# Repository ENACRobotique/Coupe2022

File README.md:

# Coupe2022
Ficihiers de KiCAD et autres pour la coupe de robotique 2022 (Age of Bots)

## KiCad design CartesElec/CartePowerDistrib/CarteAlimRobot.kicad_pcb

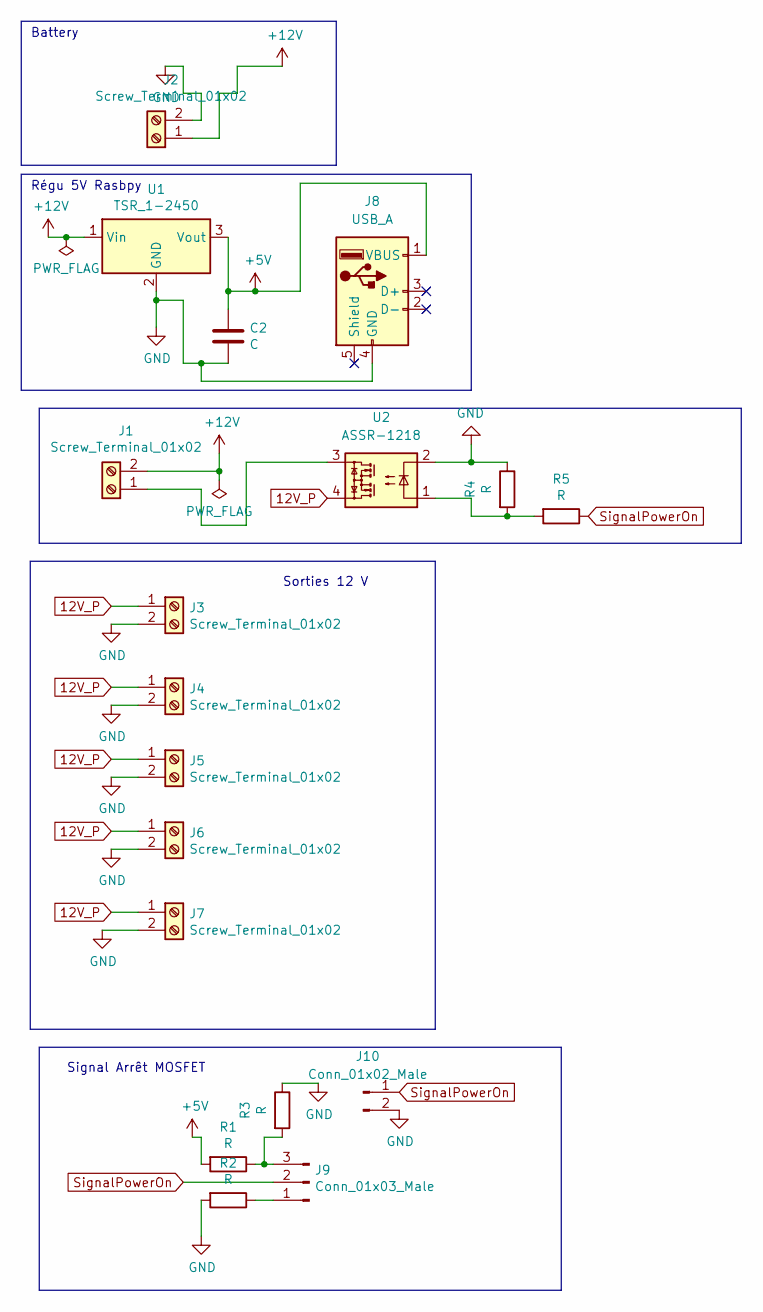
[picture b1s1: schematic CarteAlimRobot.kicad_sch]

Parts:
C2: C; C_0805_2012Metric
J1, J2, J3, J4, J5, J6, J7: Screw_Terminal_01x02; TerminalBlock_bornier-2_P5.08mm
J8: USB_A; USB_A_Molex_67643_Horizontal
J9: Conn_01x03_Male; JST_XH_B3B-XH-AM_1x03_P2.50mm_Vertical
J10: Conn_01x02_Male; JST_EH_B2B-EH-A_1x02_P2.50mm_Vertical
R1, R2, R3, R4, R5: R; R_0805_2012Metric
U1: TSR_1-2450; Converter_DCDC_TRACO_TSR-1_THT
U2: ASSR-1218; SO-4_4.4x3.6mm_P2.54mm

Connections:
12V_P: J3.1, J4.1, J5.1, J6.1, J7.1, U2.4
+5V: C2.1, J8.1 (VBUS), R1.2, U1.3 (Vout)
+12V: J1.2, J2.1, U1.1 (Vin)
GND: C2.2, J2.2, J3.2, J4.2, J5.2, J6.2, J7.2, J8.4 (GND), J10.2, R2.2, R3.1, R4.1, U1.2 (GND), U2.2
unnamed: J1.1, U2.3
unnamed: J9.1, R2.1
unnamed: J9.3, R1.1, R3.2
unnamed: R4.2, R5.2, U2.1
SignalPowerOn: J9.2, J10.1, R5.1

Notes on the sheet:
Sorties 12 V
Battery
Régu 5V Rasbpy
Signal Arrêt MOSFET

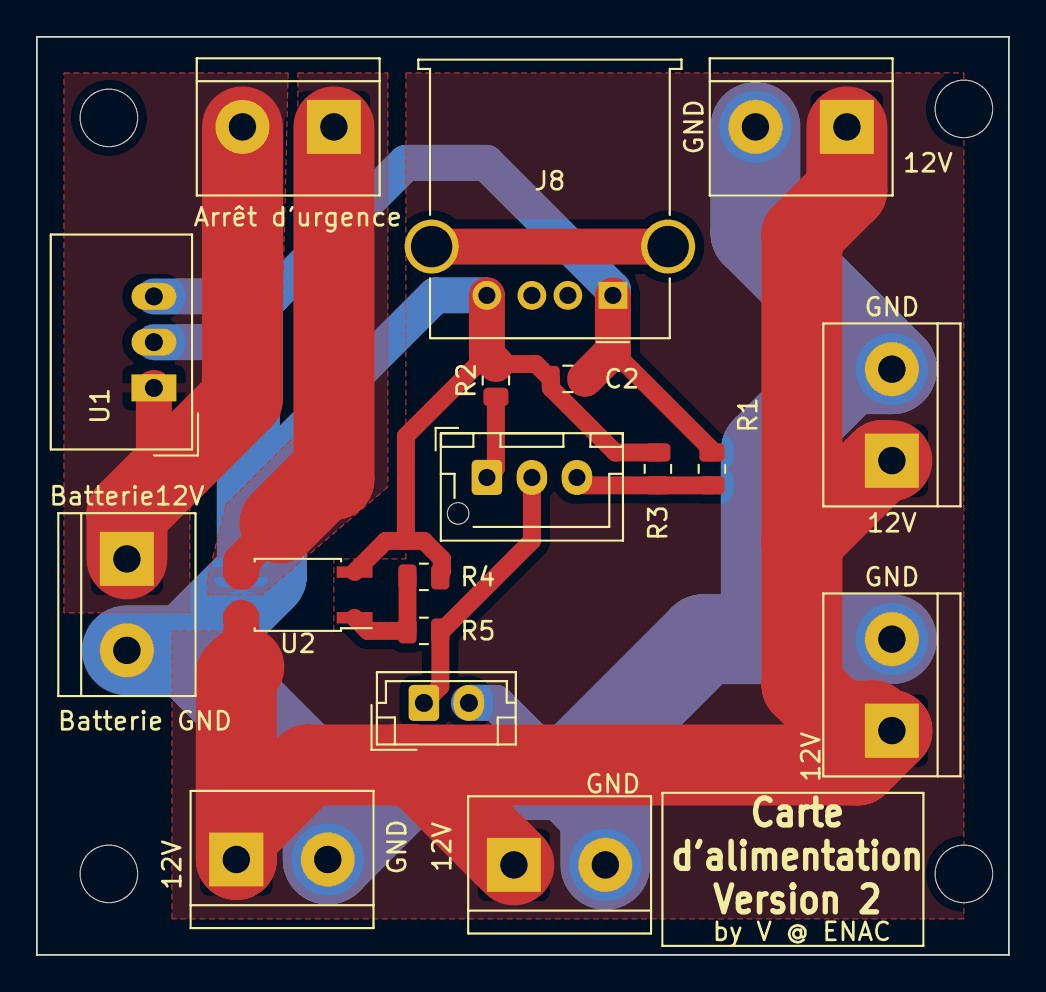
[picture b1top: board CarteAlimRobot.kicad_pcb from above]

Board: 2 copper layers, 54.0 x 51.0 mm, 18 parts (0 on the bottom side), 9 nets.

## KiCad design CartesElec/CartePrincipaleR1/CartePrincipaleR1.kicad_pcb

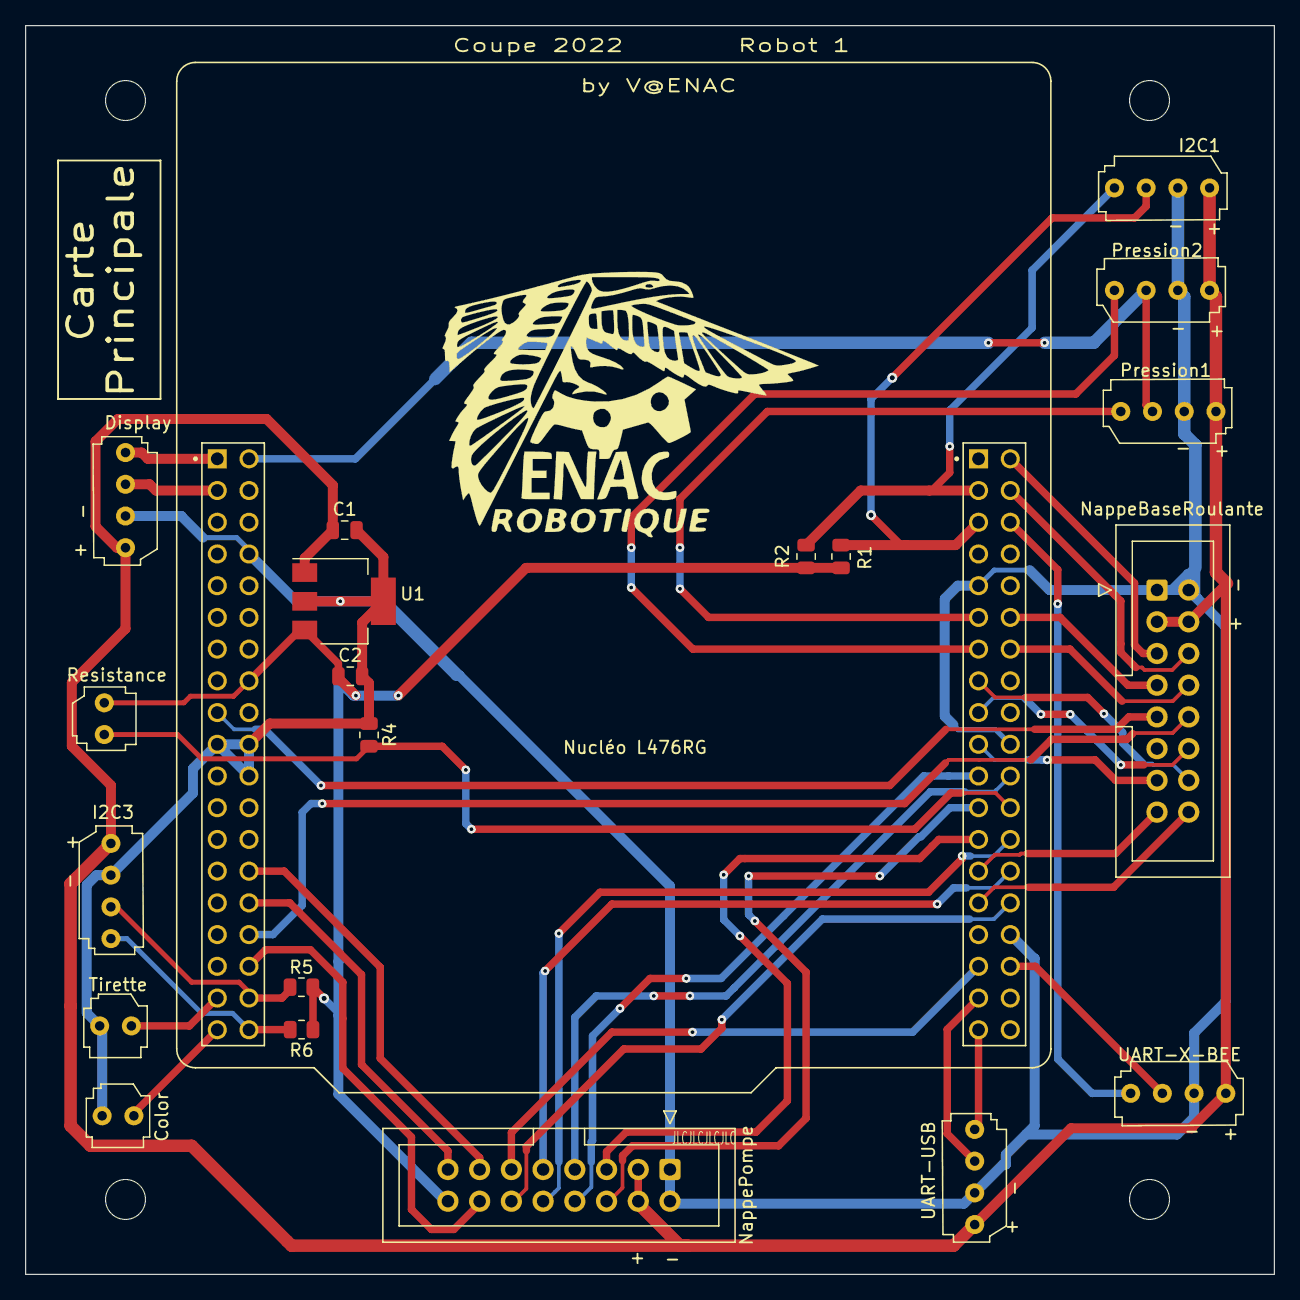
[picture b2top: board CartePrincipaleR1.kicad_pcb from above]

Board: 2 copper layers, 100.0 x 100.0 mm, 21 parts (0 on the bottom side), 41 nets.

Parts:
C1: 100n; C_0805_2012Metric
C2: 10u; C_0805_2012Metric
Color: Conn_01x02_Male; HE14_EMBASE_1x02
Display: Conn_01x04_Male; HE14_EMBASE_1x04
I2C1, I2C3: I2C; HE14_EMBASE_1x04
NappeBaseRoulante: Conn_02x08_Top_Bottom; IDC-Header_2x08_P2.54mm_Vertical
NappePompe: Conn_02x08_Top_Bottom; IDC-Header_2x08_P2.54mm_Vertical
Nucléo L476RG: NUCLEO64-F411RE; ST_NUCLEO-F401RE
Pression1, Pression2: Conn_01x04_Male; HE14_EMBASE_1x04
R1, R2, R5, R6: 2.2k; R_0805_2012Metric
R4: 1k; R_0805_2012Metric
Resistance: Conn_01x02_Male; HE14_EMBASE_1x02
Tirette: Conn_01x02_Male; HE14_EMBASE_1x02
U1: LT1129-3.3_SOT223; SOT-223-3_TabPin2
UART-USB: UART; HE14_EMBASE_1x04
UART-X-BEE: UART; HE14_EMBASE_1x04

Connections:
+3V3: C2.1, NappePompe.16, Nucléo L476RG.16 (+3V3), R1.1, R2.1, R5.1, R6.1, Resistance.1, U1.3 (VO)
+5V: C1.1, Display.1, I2C1.1, I2C3.1, NappeBaseRoulante.3, NappeBaseRoulante.4, NappePompe.3, NappePompe.4, Pression1.4, Pression2.4, U1.1 (VI), UART-USB.1, UART-X-BEE.1
A_Resistance: Nucléo L476RG.62 (PB1), R4.2, Resistance.2
CLK_Display: Display.4, Nucléo L476RG.1 (PC10)
CLK_PRESS: Nucléo L476RG.2 (PC11), Pression1.2, Pression2.2
COL_GPIO: Color.1, Nucléo L476RG.37 (PC3)
CONTACTEUR1_GPIO: NappeBaseRoulante.9, Nucléo L476RG.17 (PA15)
CONTACTEUR2_GPIO: NappeBaseRoulante.10, Nucléo L476RG.32 (PA4)
DATA_PRESS_1: Nucléo L476RG.49 (PA5), Pression1.1
DATA_PRESS_2: Nucléo L476RG.51 (PA6), Pression2.1
DIO_Display: Display.3, Nucléo L476RG.3 (PC12)
DataAX12_TX: NappeBaseRoulante.12, Nucléo L476RG.55 (PB6)
EV1: NappePompe.12, Nucléo L476RG.68 (PB13)
EV2: NappePompe.11, Nucléo L476RG.71 (PA10)
GND: C1.2, C2.2, Color.2, Display.2, I2C1.2, I2C3.2, NappeBaseRoulante.1, NappeBaseRoulante.2, NappePompe.1, NappePompe.2, Nucléo L476RG.8 (GND), Nucléo L476RG.19 (GND), Nucléo L476RG.20 (GND), Nucléo L476RG.22 (GND), Nucléo L476RG.47 (GND), Nucléo L476RG.58 (GND), Nucléo L476RG.70 (AGND), Pression1.3, Pression2.3, R4.1, Tirette.2, U1.2 (GND), UART-USB.2, UART-X-BEE.2
MC1A: NappeBaseRoulante.6, Nucléo L476RG.42 (PC6)
MC1B: NappeBaseRoulante.5, Nucléo L476RG.40 (PC8)
MC2A: NappeBaseRoulante.8, Nucléo L476RG.52 (PA11)
MC2B: NappeBaseRoulante.7, Nucléo L476RG.50 (PA12)
Mot1DIR: NappePompe.7, Nucléo L476RG.60 (PB2)
Mot1PWM: NappePompe.8, Nucléo L476RG.59 (PA9)
Mot2DIR: NappePompe.5, Nucléo L476RG.63 (PB10)
Mot2PWM: NappePompe.6, Nucléo L476RG.61 (PA8)
POMPE1: NappePompe.9, Nucléo L476RG.66 (PB14)
POMPE2: NappePompe.10, Nucléo L476RG.64 (PB15)
RC_1A: NappeBaseRoulante.16, Nucléo L476RG.67 (PB5)
RC_1B: NappeBaseRoulante.15, Nucléo L476RG.65 (PB4)
RC_2A: NappeBaseRoulante.14, Nucléo L476RG.53 (PA7)
RC_2B: NappeBaseRoulante.13, Nucléo L476RG.57 (PC7)
S1: NappePompe.13, Nucléo L476RG.28 (PA0)
S2: NappePompe.15, Nucléo L476RG.30 (PA1)
S3: NappePompe.14, Nucléo L476RG.34 (PB0)
SCL_I2C1: I2C1.4, Nucléo L476RG.41 (PB8), R2.2
SCL_I2C3: I2C3.4, Nucléo L476RG.38 (PC0), R6.2
SDA_I2C1: I2C1.3, Nucléo L476RG.43 (PB9), R1.2
SDA_I2C3: I2C3.3, Nucléo L476RG.36 (PC1), R5.2
TIR_GPIO: Nucléo L476RG.35 (PC2), Tirette.1
USART_RX: Nucléo L476RG.75 (STLINK_UART_RX/PA3), UART-USB.4
USART_TX: Nucléo L476RG.73 (STLINK_UART_TX/PA2), UART-USB.3
XBeeTx: Nucléo L476RG.72 (PC4), UART-X-BEE.3
XbeeRx: Nucléo L476RG.44 (PC5), UART-X-BEE.4

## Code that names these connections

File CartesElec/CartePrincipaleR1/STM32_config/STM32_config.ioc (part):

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Mcu.Name=STM32L476R(C-E-G)Tx
Mcu.Package=LQFP64
Mcu.UserName=STM32L476RGTx
PA0.Signal=S_TIM2_CH1
PA1.Signal=S_TIM2_CH2
PA13\ (JTMS-SWDIO).GPIOParameters=GPIO_Label
PA13\ (JTMS-SWDIO).GPIO_Label=TMS
PA13\ (JTMS-SWDIO).Mode=Serial_Wire
PA13\ (JTMS-SWDIO).Signal=SYS_JTMS-SWDIO
PA14\ (JTCK-SWCLK).GPIOParameters=GPIO_Label
PA14\ (JTCK-SWCLK).GPIO_Label=TCK
PA14\ (JTCK-SWCLK).Mode=Serial_Wire
PA14\ (JTCK-SWCLK).Signal=SYS_JTCK-SWCLK
PA2.GPIOParameters=GPIO_Speed,GPIO_PuPd,GPIO_Label,GPIO_Mode
PA2.GPIO_Label=USART_TX
PA2.GPIO_Mode=GPIO_MODE_AF_PP
PA2.GPIO_PuPd=GPIO_NOPULL
PA2.GPIO_Speed=GPIO_SPEED_FREQ_VERY_HIGH
PA2.Mode=Asynchronous
PA2.Signal=USART2_TX
PA3.GPIOParameters=GPIO_Speed,GPIO_PuPd,GPIO_Label,GPIO_Mode
PA3.GPIO_Label=USART_RX
PA3.GPIO_Mode=GPIO_MODE_AF_PP
PA3.GPIO_PuPd=GPIO_NOPULL
PA3.GPIO_Speed=GPIO_SPEED_FREQ_VERY_HIGH
PA3.Mode=Asynchronous
PA3.Signal=USART2_RX
PA5.GPIOParameters=GPIO_Speed,GPIO_PuPd,GPIO_Label,GPIO_ModeDefaultOutputPP
PA5.GPIO_Label=LD2 [green Led]
PA5.GPIO_ModeDefaultOutputPP=GPIO_MODE_OUTPUT_PP
PA5.GPIO_PuPd=GPIO_NOPULL
PA5.GPIO_Speed=GPIO_SPEED_FREQ_LOW
PA5.Signal=GPIO_Output
PA8.GPIOParameters=GPIO_Label
PA8.GPIO_Label=MOT2PWM
PA8.Signal=S_TIM1_CH1
PA9.GPIOParameters=GPIO_Label
PA9.GPIO_Label=MOT1PWM
PA9.Signal=S_TIM1_CH2
PB10.GPIOParameters=GPIO_Label
PB10.GPIO_Label=MOT2DIR
PB10.Signal=GPIO_Output
PB3\ (JTDO-TRACESWO).GPIOParameters=GPIO_Label
PB3\ (JTDO-TRACESWO).GPIO_Label=SWO
PB3\ (JTDO-TRACESWO).Signal=SYS_JTDO-SWO
PC0.Signal=I2C3_SCL
PC1.Signal=I2C3_SDA
PC13.GPIOParameters=GPIO_PuPd,GPIO_Label,GPIO_ModeDefaultEXTI
PC13.GPIO_Label=B1 [Blue PushButton]
PC13.GPIO_ModeDefaultEXTI=GPIO_MODE_IT_FALLING
PC13.GPIO_PuPd=GPIO_NOPULL
PC13.Signal=GPXTI13
PC14-OSC32_IN\ (PC14).Mode=LSE-External-Oscillator
PC14-OSC32_IN\ (PC14).Signal=RCC_OSC32_IN
PC15-OSC32_OUT\ (PC15).Mode=LSE-External-Oscillator
PC15-OSC32_OUT\ (PC15).Signal=RCC_OSC32_OUT
PC4.GPIOParameters=GPIO_Label
PC4.GPIO_Label=ADC_2
PC4.Signal=ADCx_IN13
PC5.GPIOParameters=GPIO_Label
PC5.GPIO_Label=ADC_1
PC5.Signal=ADCx_IN14
PC6.GPIOParameters=GPIO_Label
PC6.GPIO_Label=MOT1_ENC_A
PC6.Signal=GPIO_Input
PC7.GPIOParameters=GPIO_Label
PC7.GPIO_Label=MOT1DIR
PC7.Signal=GPIO_Output
PH0-OSC_IN\ (PH0).Signal=RCC_OSC_IN
PH1-OSC_OUT\ (PH1).Signal=RCC_OSC_OUT
RCC.HSE_VALUE=8000000
RCC.SYSCLKFreq_VALUE=80000000
RCC.SYSCLKSource=RCC_SYSCLKSOURCE_PLLCLK
board=NUCLEO-L476RG
boardIOC=true

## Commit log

2021-10-24 Début du Répo
2021-10-24 Mise à jour du PCB + début d'optimisation
2021-10-24 Optimisation d'espace sur la carte d'alim
2021-10-24 Save
2022-01-18 Ajout d'un nouveau projet
2022-01-18 fin de la carte d'alim
2022-01-18 Changement de description
2022-01-27 update maybe?
2022-01-29 update carte nucleo F411RE
2022-01-30 update hierarchical
2022-02-01 small updates
2022-02-02 [carte robot 1] finish schematic.
2022-02-02 Add HE14 footprints.
2022-02-03 Carte principale finie
2022-02-03 Ajout de textes au PCB
2022-02-03 carte secondair update
2022-02-03 secondaire update
2022-02-03 error fix
2022-02-03 footprint fixes
2022-02-03 gereber update
2022-02-04 Ajout de la date
2022-02-04 Ajout de cotes à la carte principale pour aider le gars qui integrera ce truc sous solidworks
2022-02-04 Changement mineur
2022-02-06 update carte sec
2022-02-06 commit chelou
2022-02-06 update PCB masse
2022-02-06 relecture
2022-02-06 cartePrincipale Update
2022-02-06 carte secondaire terminé
2022-02-06 Modif dernière minute
2022-02-06 UPDATE GERBER
2022-04-08 updating file and adding remote sending stlink
2022-04-08 updating remote
2022-04-13 sending remote improvement
2022-04-13 updating sendremote cdmd
2022-04-13 remote update
2022-04-24 Carte Alim V2
2022-04-24 Carte Alim V2.1\nAjout d'un interrupteur pour la RaspbPi
2022-04-27 update remote
2022-05-11 Ajout du code de la vitrine à ce répo
2022-05-12 Code des LEDS amélioré
2022-05-13 Mise à jour
